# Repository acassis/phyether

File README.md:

phyether
========

This is an Ethernet PHY board based on Andy Brown board: http://andybrown.me.uk/wk/2012/09/01/ethernet-phy-stm32f107/

I used KiCAD to develop this board. KiCAD is open-source and it is a very powerful EDA software.

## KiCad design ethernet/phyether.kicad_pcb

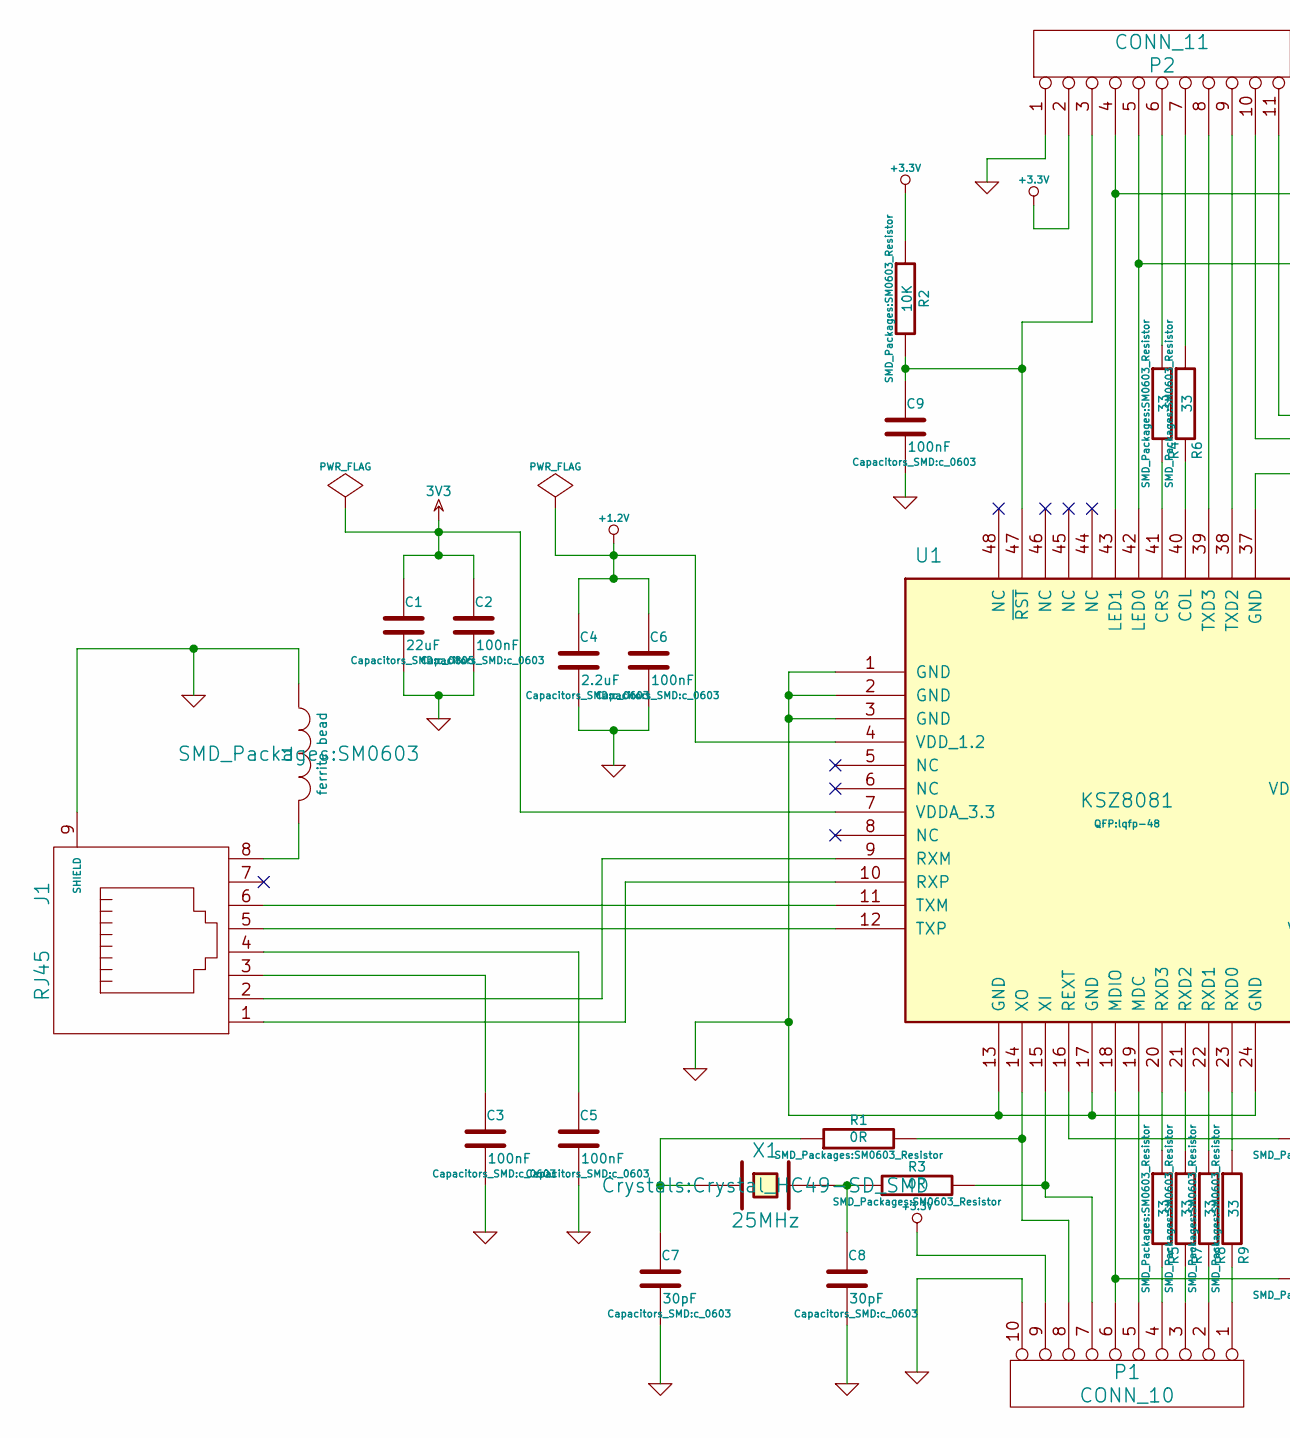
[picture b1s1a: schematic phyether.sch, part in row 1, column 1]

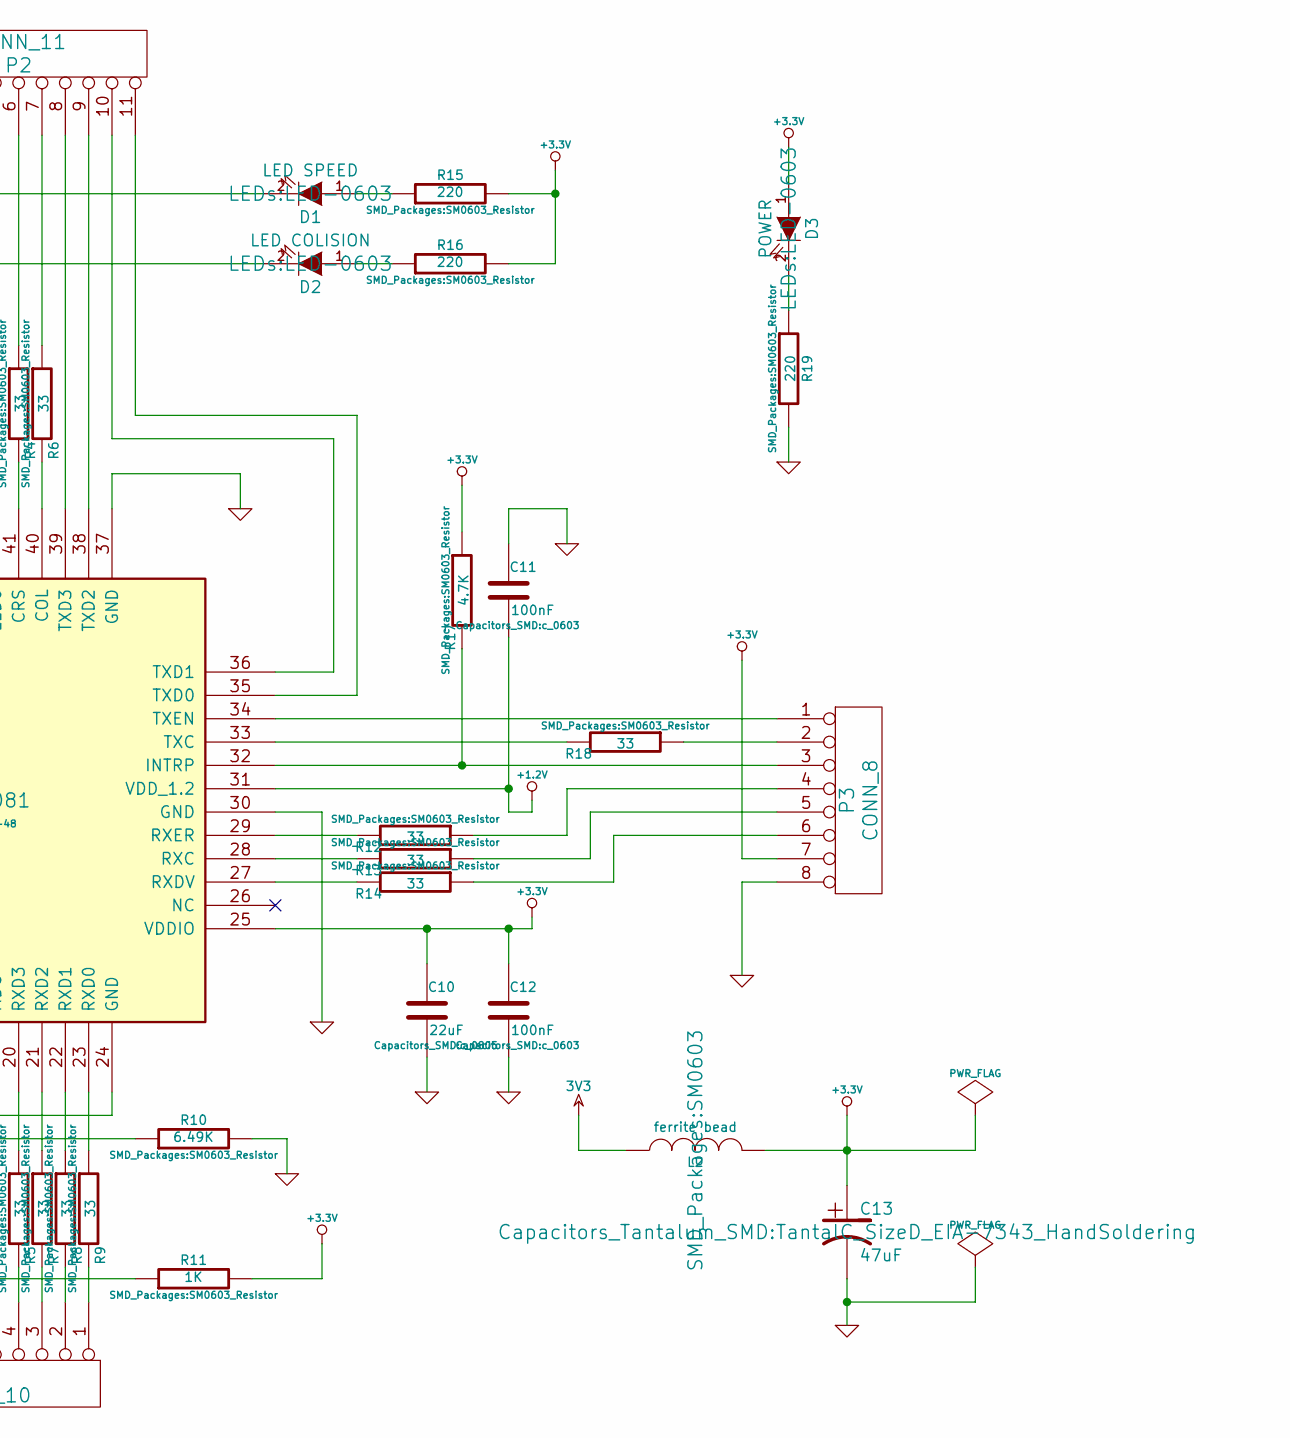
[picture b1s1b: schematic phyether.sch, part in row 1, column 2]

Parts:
C1, C10: 22uF; c_0805
C2, C3, C5, C6, C9, C11, C12: 100nF; c_0603
C4: 2.2uF; c_0603
C7, C8: 30pF; c_0603
C13: 47uF; TantalC_SizeD_EIA-7343_HandSoldering
D1: LED SPEED; LED-0603
D2: LED COLISION; LED-0603
D3: POWER; LED-0603
J1: RJ45; RJ45_8
L1, L2: ferrite bead; SM0603
P1: CONN_10; Pin_Header_Straight_1x10
P2: CONN_11; Pin_Header_Straight_1x11
P3: CONN_8; Pin_Header_Straight_1x08
R1, R3: 0R; SM0603_Resistor
R2: 10K; SM0603_Resistor
R4, R5, R6, R7, R8, R9, R12, R13, R14, R18: 33; SM0603_Resistor
R10: 6.49K; SM0603_Resistor
R11: 1K; SM0603_Resistor
R15, R16, R19: 220; SM0603_Resistor
R17: 4.7K; SM0603_Resistor
U1: KSZ8081; lqfp-48
X1: 25MHz; Crystal_HC49-SD_SMD

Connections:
3V3: C1.1, C2.1, L2.1, U1.7 (VDDA_3.3)
+1.2V: C4.1, C6.1, C11.2, U1.4 (VDD_1.2), U1.31 (VDD_1.2)
+3.3V: C10.1, C12.1, C13.1, D3.1 (A), L2.2, P1.9, P2.2, P3.7, R2.1, R11.2, R15.2, R16.2, R17.1, U1.25 (VDDIO)
GND: C1.2, C2.2, C3.2, C4.2, C5.2, C6.2, C7.2, C8.2, C9.2, C10.2, C11.1, C12.2, C13.2, J1.9 (SHIELD), L1.1, P1.10, P2.1, P3.8, R10.2, R19.2, U1.1 (GND), U1.2 (GND), U1.3 (GND), U1.13 (GND), U1.17 (GND), U1.24 (GND), U1.30 (GND), U1.37 (GND)
unnamed: C3.1, J1.3
unnamed: C5.1, J1.4
unnamed: C7.1, R1.1, X1.1
unnamed: C8.1, R3.1, X1.2
unnamed: C9.1, P2.3, R2.2, U1.47 (~RST)
unnamed: D1.1 (A), R15.1
unnamed: D1.2 (K), P2.4, U1.43 (LED1)
unnamed: D2.1 (A), R16.1
unnamed: D2.2 (K), P2.5, U1.42 (LED0)
unnamed: D3.2 (K), R19.1
unnamed: J1.1, U1.10 (RXP)
unnamed: J1.2, U1.9 (RXM)
unnamed: J1.5, U1.12 (TXP)
unnamed: J1.6, U1.11 (TXM)
unnamed: J1.8, L1.2
unnamed: P1.1, R9.2
unnamed: P1.2, R8.2
unnamed: P1.3, R7.2
unnamed: P1.4, R5.2
unnamed: P1.5, U1.19 (MDC)
unnamed: P1.6, R11.1, U1.18 (MDIO)
unnamed: P1.7, R3.2, U1.15 (XI)
unnamed: P1.8, R1.2, U1.14 (XO)
unnamed: P2.6, R4.1
unnamed: P2.7, R6.1
unnamed: P2.8, U1.39 (TXD3)
unnamed: P2.9, U1.38 (TXD2)
unnamed: P2.10, U1.36 (TXD1)
unnamed: P2.11, U1.35 (TXD0)
unnamed: P3.1, U1.34 (TXEN)
unnamed: P3.2, R18.1
unnamed: P3.3, R17.2, U1.32 (INTRP)
unnamed: P3.4, R12.1
unnamed: P3.5, R13.1
unnamed: P3.6, R14.1
unnamed: R4.2, U1.41 (CRS)
unnamed: R5.1, U1.20 (RXD3)
unnamed: R6.2, U1.40 (COL)
unnamed: R7.1, U1.21 (RXD2)
unnamed: R8.1, U1.22 (RXD1)
unnamed: R9.1, U1.23 (RXD0)
unnamed: R10.1, U1.16 (REXT)
unnamed: R12.2, U1.29 (RXER)
unnamed: R13.2, U1.28 (RXC)
unnamed: R14.2, U1.27 (RXDV)
unnamed: R18.2, U1.33 (TXC)

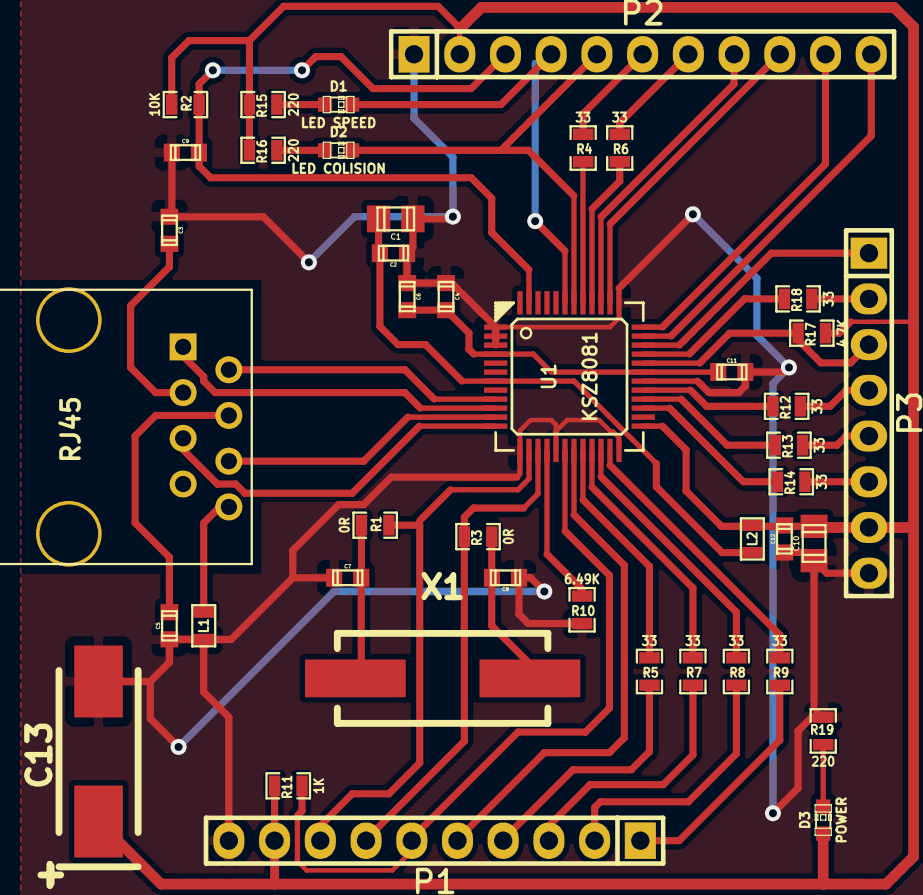
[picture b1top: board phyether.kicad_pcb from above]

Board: 2 copper layers, 43 parts (0 on the bottom side), 50 nets.

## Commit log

2014-08-19 Add KiCAD Ethernet PHY design files
